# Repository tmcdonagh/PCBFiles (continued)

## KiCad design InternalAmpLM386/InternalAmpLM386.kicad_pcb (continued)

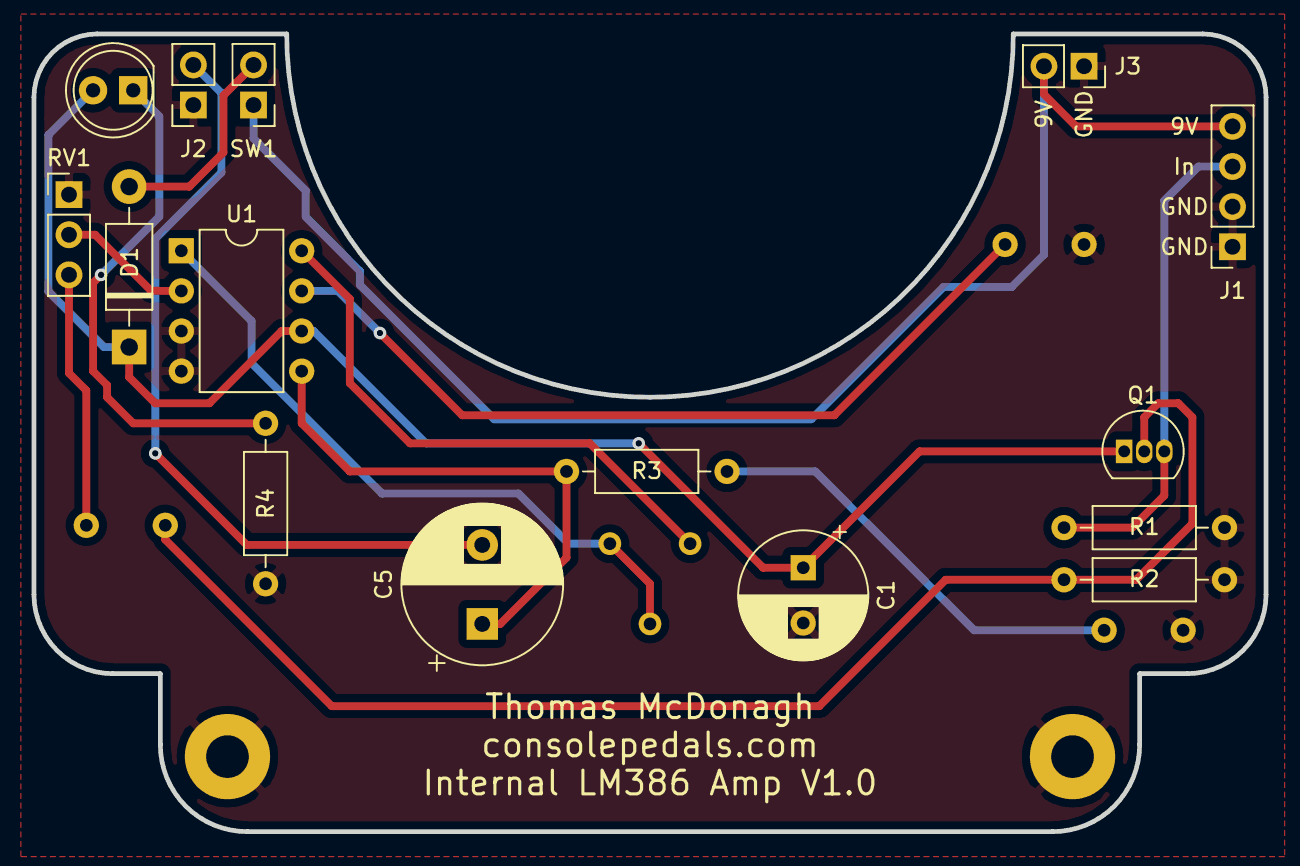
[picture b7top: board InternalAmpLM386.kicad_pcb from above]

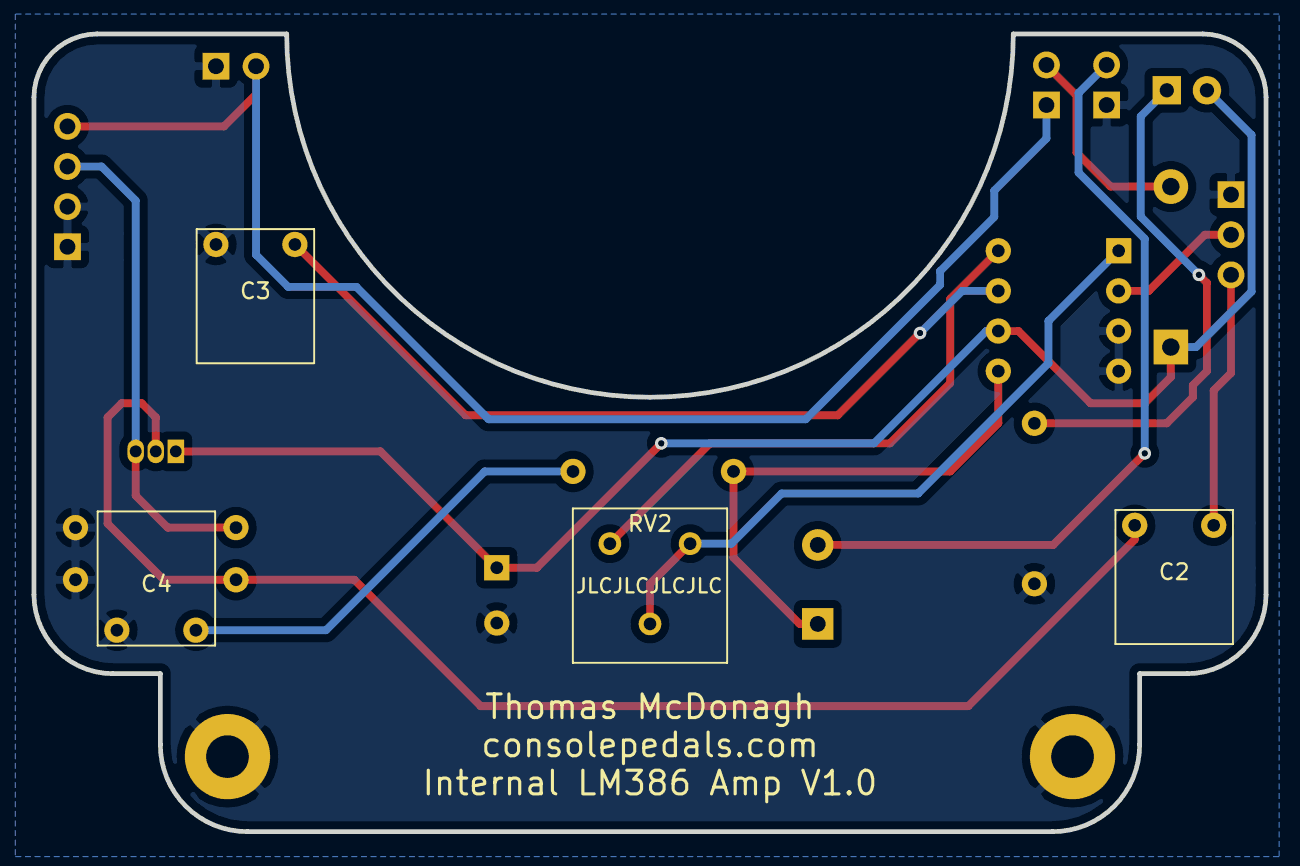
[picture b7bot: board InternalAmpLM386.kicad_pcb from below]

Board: 2 copper layers, 78.0 x 50.5 mm, 21 parts (4 on the bottom side), 15 nets.
